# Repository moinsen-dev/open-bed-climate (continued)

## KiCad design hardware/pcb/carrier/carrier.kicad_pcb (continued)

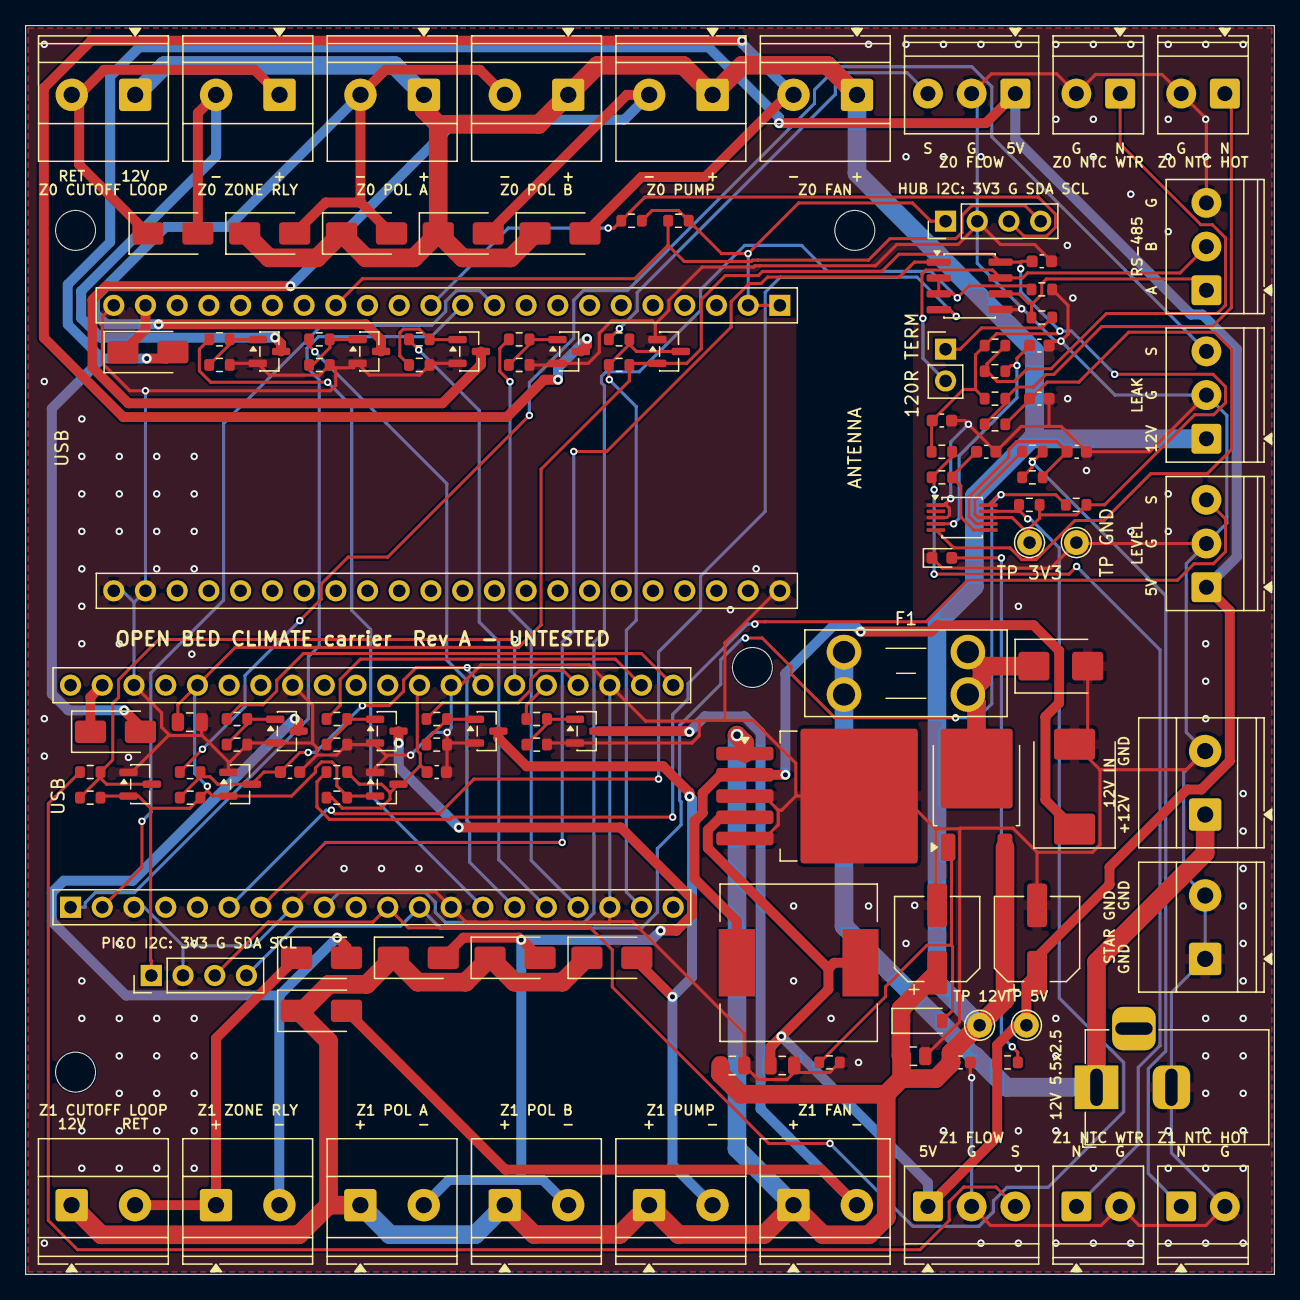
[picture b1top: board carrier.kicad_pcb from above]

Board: 2 copper layers, 100.0 x 100.0 mm, 126 parts (0 on the bottom side), 66 nets.

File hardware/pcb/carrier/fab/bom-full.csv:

Qty,Value,Designators,Footprint,LCSC,LCSC verified,Assembly,Note
1,Raspberry Pi Pico 2,U1,RaspberryPi_Pico2_Socket,,,hand-solder / THT,"Socket: 2x 1x20 female header 2.54 mm (hand-soldered), Pico 2 with male headers plugs in"
1,ESP32-S3-DevKitC-1,U2,ESP32-S3-DevKitC-1_Socket,,,hand-solder / THT,Socket: 2x 1x22 female header 2.54 mm (hand-soldered)
1,"12V IN 5.5x2.5 (Solo only, <=5 A)",J1,BarrelJack_Horizontal,,,hand-solder / THT,
1,12V IN,J2,"TerminalBlock_Phoenix_MKDS-1,5-2-5.08_1x02_P5.08mm_Horizontal",,,hand-solder / THT,
1,STAR GND,J3,"TerminalBlock_Phoenix_MKDS-1,5-2-5.08_1x02_P5.08mm_Horizontal",,,hand-solder / THT,
1,5A mini blade,F1,Fuseholder_Blade_Mini_Keystone_3568,,,hand-solder / THT,"Keystone 3568 holder + ATM mini blade fuse: 5 A on 1 oz copper, 7.5 A only on 2 oz"
1,SMBJ15A,D1,D_SMB,C699013,yes,JLC SMT,TVS: clamps transients; a 24 V brick plugged in by mistake makes it conduct and blows the fuse
1,AOD4185,Q1,TO-252-2,,,JLC SMT,"Reverse-polarity P-FET, -40 V, <= 15 mOhm, TO-252: ~0.7 W at 7 A on its copper. LCSC number to pick"
1,BZT52C12,D2,D_SOD-123,,,JLC SMT,"Gate clamp, V_GS <= 12 V"
6,10k,"R1,R15,R18,R20,R30,R40",R_0603_1608Metric,C25804,yes,JLC SMT,
9,100n,"C1,C8,C9,C10,C11,C12,C13,C14,C15",C_0603_1608Metric,C14663,yes,JLC SMT,
1,LM2596S-5.0,U3,TO-263-5_TabPin3,C116713,yes,JLC SMT,
1,100u 35V,C2,CP_Elec_6.3x7.7,,,JLC SMT,"Bulk input cap, aluminium electrolytic low ESR; LCSC number to pick"
3,10u,"C3,C4,C7",C_0805_2012Metric,C15850,check,JLC SMT,
1,SS54,D3,D_SMC,,,JLC SMT,Catch diode 5 A 40 V; LCSC number to pick
1,33uH 4A,L1,L_12x12mm_H8mm,,,JLC SMT,"Shielded power inductor, I_sat >= 4 A; LCSC number to pick"
1,220u 16V,C5,CP_Elec_6.3x7.7,,,JLC SMT,"Output cap, needs some ESR (LM2596 is voltage-mode); LCSC number to pick"
1,22u,C6,C_0805_2012Metric,C45783,check,JLC SMT,
9,1k,"R2,R6,R8,R10,R12,R17,R19,R29,R39",R_0603_1608Metric,C21190,check,JLC SMT,
1,PWR 5V,D4,LED_0603_1608Metric,C2286,check,JLC SMT,
12,SS34,"D5,D6,D9,D10,D11,D12,D13,D15,D16,D17,D18,D19",D_SMA,C8678,yes,JLC SMT,
1,TP 12V,TP1,TestPoint_THTPad_D2.0mm_Drill1.0mm,,,hand-solder / THT,
1,TP 5V,TP2,TestPoint_THTPad_D2.0mm_Drill1.0mm,,,hand-solder / THT,
1,TP 3V3,TP3,TestPoint_THTPad_D2.0mm_Drill1.0mm,,,hand-solder / THT,
1,TP GND,TP4,TestPoint_THTPad_D2.0mm_Drill1.0mm,,,hand-solder / THT,
1,ADS1115IDGSR,U4,MSOP-10_3x3mm_P0.5mm,C37593,yes,JLC SMT,
12,4.7k,"R3,R4,R13,R14,R22,R24,R26,R28,R32,R34,R36,R38",R_0603_1608Metric,C23162,check,JLC SMT,
4,10k 0.1%,"R5,R7,R9,R11",R_0603_1608Metric,,,JLC SMT,
1,Z0 NTC WATER,J4,"TerminalBlock_Phoenix_PT-1,5-2-3.5-H_1x02_P3.50mm_Horizontal",,,hand-solder / THT,
1,Z0 NTC HOT,J5,"TerminalBlock_Phoenix_PT-1,5-2-3.5-H_1x02_P3.50mm_Horizontal",,,hand-solder / THT,
1,Z1 NTC WATER,J6,"TerminalBlock_Phoenix_PT-1,5-2-3.5-H_1x02_P3.50mm_Horizontal",,,hand-solder / THT,
1,Z1 NTC HOT,J7,"TerminalBlock_Phoenix_PT-1,5-2-3.5-H_1x02_P3.50mm_Horizontal",,,hand-solder / THT,
1,I2C PICO (3V3 GND SDA SCL),J8,PinHeader_1x04_P2.54mm_Vertical,,,hand-solder / THT,
1,I2C HUB SHT45 (3V3 GND SDA SCL),J9,PinHeader_1x04_P2.54mm_Vertical,,,hand-solder / THT,
1,SP3485EN,U5,SOIC-8_3.9x4.9mm_P1.27mm,C8963,yes,JLC SMT,
1,120,R16,R_0603_1608Metric,C22787,check,JLC SMT,
1,TERM 120R,JP1,PinHeader_1x02_P2.54mm_Vertical,,,hand-solder / THT,Fit a jumper only if this end of the bus has no other termination
1,RS485 A B GND,J10,"TerminalBlock_Phoenix_PT-1,5-3-3.5-H_1x03_P3.50mm_Horizontal",,,hand-solder / THT,
4,BAT54S,"D7,D8,D14,D20",SOT-23,C916425,yes,JLC SMT,
1,LEAK +12V GND SIG,J11,"TerminalBlock_Phoenix_PT-1,5-3-3.5-H_1x03_P3.50mm_Horizontal",,,hand-solder / THT,
1,LEVEL +5V GND SIG,J12,"TerminalBlock_Phoenix_PT-1,5-3-3.5-H_1x03_P3.50mm_Horizontal",,,hand-solder / THT,
8,220,"R21,R23,R25,R27,R31,R33,R35,R37",R_0603_1608Metric,C22962,check,JLC SMT,
8,AO3400A,"Q2,Q3,Q4,Q5,Q6,Q7,Q8,Q9",SOT-23,C20917,yes,JLC SMT,
1,Z0 CUTOFF LOOP,J13,"TerminalBlock_Phoenix_MKDS-1,5-2-5.08_1x02_P5.08mm_Horizontal",,,hand-solder / THT,
1,Z0 ZONE RELAY COIL,J14,"TerminalBlock_Phoenix_MKDS-1,5-2-5.08_1x02_P5.08mm_Horizontal",,,hand-solder / THT,
1,Z0 POL A,J15,"TerminalBlock_Phoenix_MKDS-1,5-2-5.08_1x02_P5.08mm_Horizontal",,,hand-solder / THT,
1,Z0 POL B,J16,"TerminalBlock_Phoenix_MKDS-1,5-2-5.08_1x02_P5.08mm_Horizontal",,,hand-solder / THT,
1,Z0 PUMP,J17,"TerminalBlock_Phoenix_MKDS-1,5-2-5.08_1x02_P5.08mm_Horizontal",,,hand-solder / THT,
1,Z0 FAN,J18,"TerminalBlock_Phoenix_MKDS-1,5-2-5.08_1x02_P5.08mm_Horizontal",,,hand-solder / THT,
1,Z0 FLOW +5V GND SIG,J19,"TerminalBlock_Phoenix_PT-1,5-3-3.5-H_1x03_P3.50mm_Horizontal",,,hand-solder / THT,
1,Z1 CUTOFF LOOP,J20,"TerminalBlock_Phoenix_MKDS-1,5-2-5.08_1x02_P5.08mm_Horizontal",,,hand-solder / THT,
1,Z1 ZONE RELAY COIL,J21,"TerminalBlock_Phoenix_MKDS-1,5-2-5.08_1x02_P5.08mm_Horizontal",,,hand-solder / THT,
1,Z1 POL A,J22,"TerminalBlock_Phoenix_MKDS-1,5-2-5.08_1x02_P5.08mm_Horizontal",,,hand-solder / THT,
1,Z1 POL B,J23,"TerminalBlock_Phoenix_MKDS-1,5-2-5.08_1x02_P5.08mm_Horizontal",,,hand-solder / THT,
1,Z1 PUMP,J24,"TerminalBlock_Phoenix_MKDS-1,5-2-5.08_1x02_P5.08mm_Horizontal",,,hand-solder / THT,
1,Z1 FAN,J25,"TerminalBlock_Phoenix_MKDS-1,5-2-5.08_1x02_P5.08mm_Horizontal",,,hand-solder / THT,
1,Z1 FLOW +5V GND SIG,J26,"TerminalBlock_Phoenix_PT-1,5-3-3.5-H_1x03_P3.50mm_Horizontal",,,hand-solder / THT,
